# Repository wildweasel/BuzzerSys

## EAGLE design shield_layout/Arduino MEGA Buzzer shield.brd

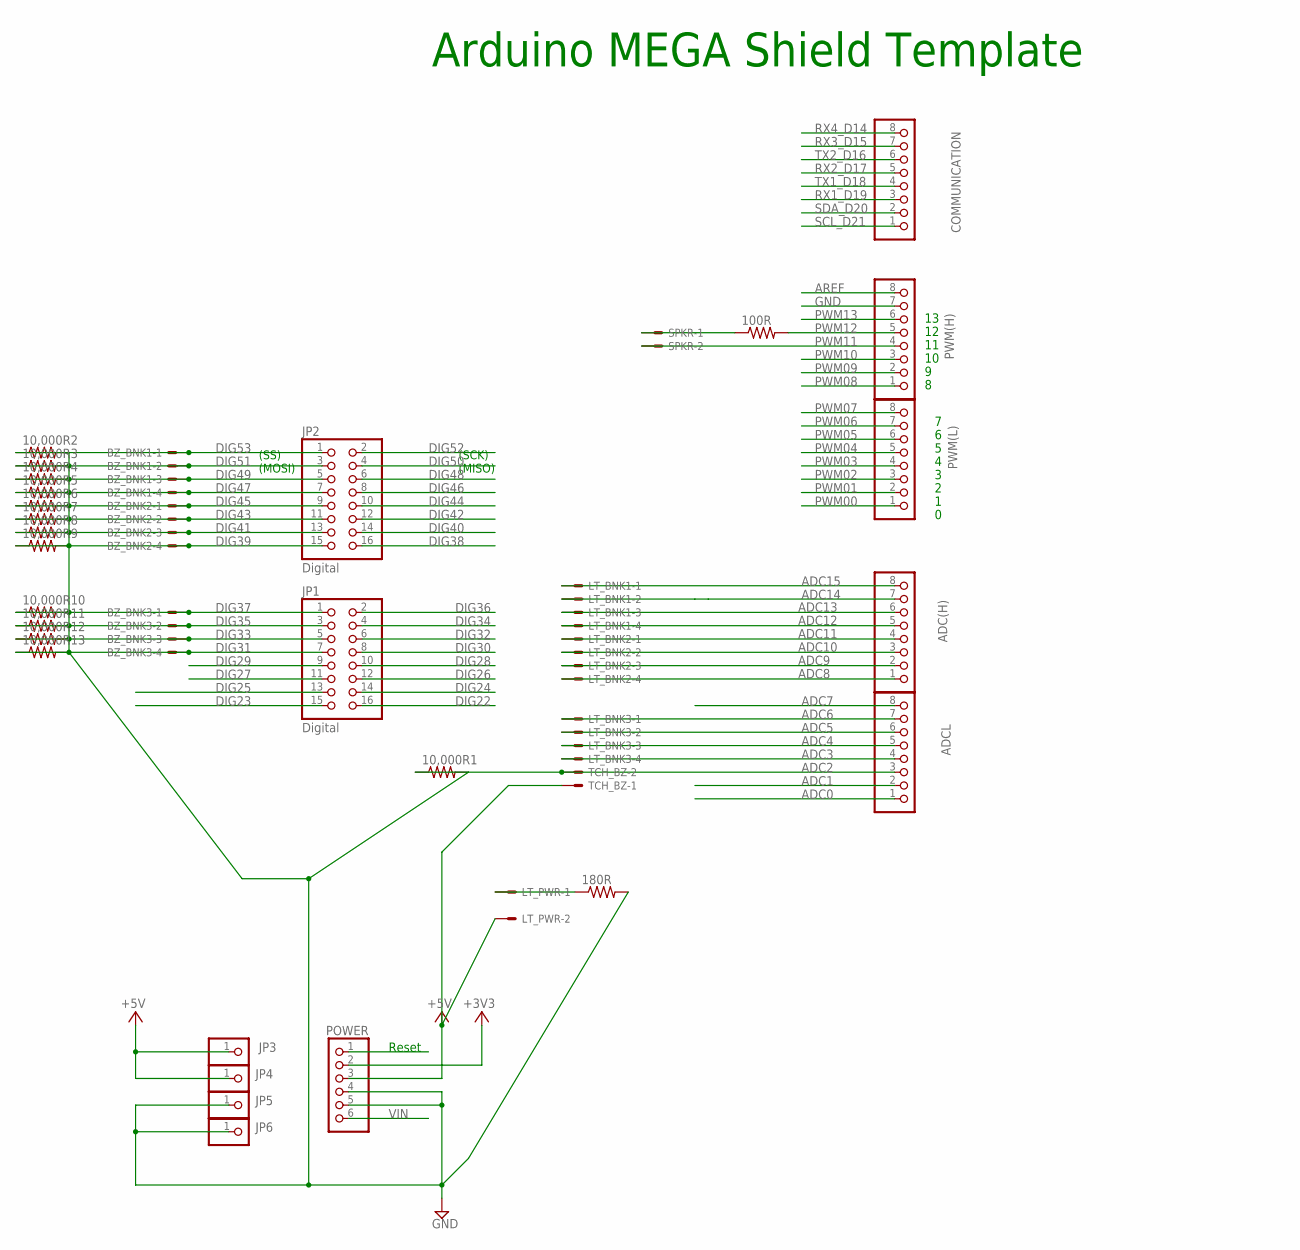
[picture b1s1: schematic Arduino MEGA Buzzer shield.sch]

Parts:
10,000R1, 10,000R2, 10,000R3, 10,000R4, 10,000R5, 10,000R6, 10,000R7, 10,000R8, 10,000R9, 10,000R10, 10,000R11, 10,000R12, 10,000R13, 100R, 180R: R-US_0204/2V; 0204V
ADC(H): PINHD-1X8; 1X08
ADCL: PINHD-1X8; 1X08
BZ_BNK1, BZ_BNK2, BZ_BNK3: KK-156-4
COMMUNICATION: PINHD-1X8; 1X08
JP1, JP2: Digital; 2X08
JP3, JP4, JP5, JP6: PINHD-1X1; 1X01
LT_BNK1, LT_BNK2, LT_BNK3: KK-156-4
LT_PWR: KK-156-2
POWER: PINHD-1X6; 1X06
PWM(H): PINHD-1X8; 1X08
PWM(L): PINHD-1X8; 1X08
SPKR: KK-156-2
TCH_BZ: KK-156-2

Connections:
+3V3: POWER.2
+5V: JP3.1, JP4.1, LT_PWR.2, POWER.3, TCH_BZ.1
ADC0: ADCL.1
ADC1: ADCL.2
ADC2: 10,000R1.1, ADCL.3, TCH_BZ.2
ADC3: ADCL.4, LT_BNK3.4
ADC4: ADCL.5, LT_BNK3.3
ADC5: ADCL.6, LT_BNK3.2
ADC6: ADCL.7, LT_BNK3.1
ADC7: ADCL.8
ADC8: ADC(H).1, LT_BNK2.4
ADC9: ADC(H).2, LT_BNK2.3
ADC10: ADC(H).3, LT_BNK2.2
ADC11: ADC(H).4, LT_BNK2.1
ADC12: ADC(H).5, LT_BNK1.4
ADC13: ADC(H).6, LT_BNK1.3
ADC14: ADC(H).7, LT_BNK1.2
ADC15: ADC(H).8, LT_BNK1.1
AREF: PWM(H).8
DIG22: JP1.16
DIG23: JP1.15
DIG24: JP1.14
DIG25: JP1.13
DIG26: JP1.12
DIG27: JP1.11
DIG28: JP1.10
DIG29: JP1.9
DIG30: JP1.8
DIG31: 10,000R13.1, BZ_BNK3.4, JP1.7
DIG32: JP1.6
DIG33: 10,000R12.1, BZ_BNK3.3, JP1.5
DIG34: JP1.4
DIG35: 10,000R11.1, BZ_BNK3.2, JP1.3
DIG36: JP1.2
DIG37: 10,000R10.1, BZ_BNK3.1, JP1.1
DIG38: JP2.16
DIG39: 10,000R9.1, BZ_BNK2.4, JP2.15
DIG40: JP2.14
DIG41: 10,000R8.1, BZ_BNK2.3, JP2.13
DIG42: JP2.12
DIG43: 10,000R7.1, BZ_BNK2.2, JP2.11
DIG44: JP2.10
DIG45: 10,000R6.1, BZ_BNK2.1, JP2.9
DIG46: JP2.8
DIG47: 10,000R5.1, BZ_BNK1.4, JP2.7
DIG48: JP2.6
DIG49: 10,000R4.1, BZ_BNK1.3, JP2.5
DIG50: JP2.4
DIG51: 10,000R3.1, BZ_BNK1.2, JP2.3
DIG52: JP2.2
DIG53: 10,000R2.1, BZ_BNK1.1, JP2.1
GND: 10,000R1.2, 10,000R2.2, 10,000R3.2, 10,000R4.2, 10,000R5.2, 10,000R6.2, 10,000R7.2, 10,000R8.2, 10,000R9.2, 10,000R10.2, 10,000R11.2, 10,000R12.2, 10,000R13.2, 180R.2, JP5.1, JP6.1, POWER.4, POWER.5, PWM(H).7
unnamed: 180R.1, LT_PWR.1
PWM00: PWM(L).1
PWM01: PWM(L).2
PWM02: PWM(L).3
PWM03: PWM(L).4
PWM04: PWM(L).5
PWM05: PWM(L).6
PWM06: PWM(L).7
PWM07: PWM(L).8
PWM08: PWM(H).1
PWM09: PWM(H).2
PWM10: PWM(H).3
PWM11: PWM(H).4, SPKR.2
PWM12: 100R.2, PWM(H).5
PWM13: PWM(H).6
RESET: POWER.1
RX1_D19: COMMUNICATION.3
RX2_D17: COMMUNICATION.5
RX3_D15: COMMUNICATION.7
RX4_D14: COMMUNICATION.8
SCL_D21: COMMUNICATION.1
SDA_D20: COMMUNICATION.2
SPKR$1: 100R.1, SPKR.1
TX1_D18: COMMUNICATION.4
TX2_D16: COMMUNICATION.6
VIN: POWER.6

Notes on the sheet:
Arduino MEGA Shield Template
(SS)
(MOSI)
(SCK)
(MISO)
Reset

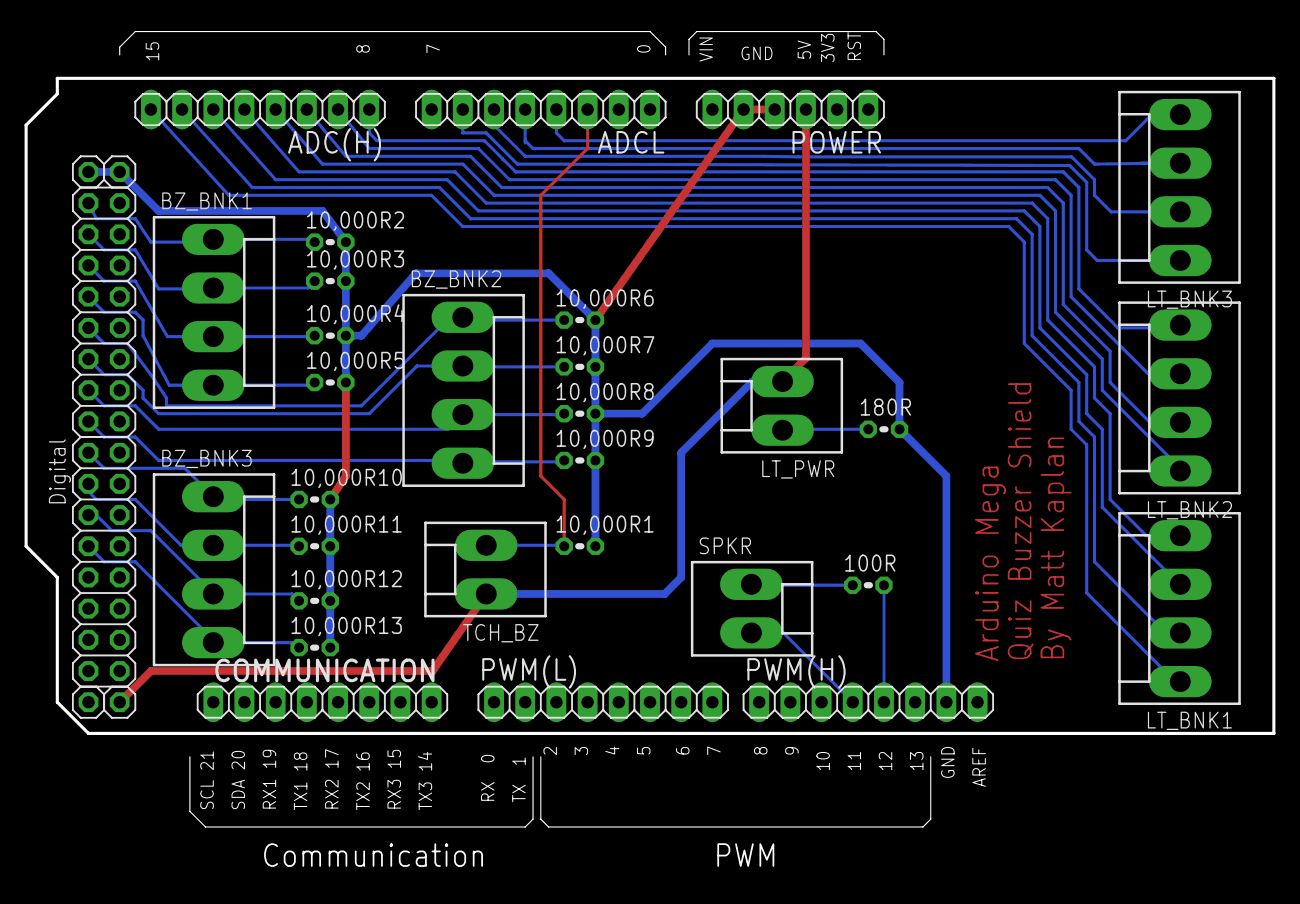
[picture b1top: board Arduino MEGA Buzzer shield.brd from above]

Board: 2 copper layers, 101.6 x 69.3 mm, 36 parts (0 on the bottom side), 31 nets.

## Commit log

2018-01-20 rename ino to match folder
2018-08-11 old update?
2018-08-11 add EAGLE buzzer shield board layout
2018-09-16 update buzzer shield board layout to resize molex connectors and resistors
2018-11-09 reorg w/ hardware fixes; more OO; better disabling teacher buzzer to prevent double press
2018-12-25 added sounds back in
